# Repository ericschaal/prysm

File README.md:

<p align="center">
  <strong>LED strips that follow your screen.</strong><br>
  Prysm reads the picture, works out a colour for each LED around the screen
  and sends those colours to WLED.
</p>

## What you need

- **A picture source:** an HDMI capture card, or a rooted LG webOS TV.
- **WLED** with LED strips around the screen.
- **For a capture card:** a Linux or macOS computer, such as a Raspberry Pi.

```text
HDMI → capture card → computer running Prysm → WLED → LEDs
LG TV running Prysm (full package) → WLED → LEDs
LG TV (slim package) → computer running Prysm → WLED → LEDs
```

## Install

| Where Prysm runs | Package | Guide |
| --- | --- | --- |
| Raspberry Pi OS, Debian, Ubuntu | `prysm-headless` `.deb` (arm64, amd64) | [Debian](docs/users/debian.md) |
| Any Linux with Docker | `ghcr.io/ericschaal/prysm-headless` | [Docker](docs/users/docker.md) |
| TrueNAS SCALE | the same image | [TrueNAS](docs/users/truenas.md) |
| A rooted LG TV | `io.prysm.tv`, full or slim | [LG TV](docs/users/webos.md) |
| macOS, or Linux from source | build `prysm-headless` | [Build](docs/developers/README.md#build-and-run) |

Packages are attached to the [GitHub releases](https://github.com/ericschaal/prysm/releases).
Then connect the picture ([capture card](docs/users/quickstart.md) or
[LG TV](docs/users/webos.md)) and run the setup wizard in the web portal
([set up your lights](docs/users/configuration.md)). Start at
[Set up Prysm](docs/users/README.md) if you are unsure which setup fits.

The web portal has no password: keep Prysm on a trusted home network.

> **Status.** Prysm 1.x has not yet been verified end to end on real hardware
> (capture cards, WLED devices and both TV packages).

## What runs where

| Program | Runs on | Does |
| --- | --- | --- |
| `prysm-headless` | Linux or macOS | The service: capture card or slim TV in, WLED out, web portal. Shipped as the `.deb` and the Docker image. |
| `prysm-tui` | Linux or macOS | The same, plus a terminal preview of what the LEDs show; for local testing. |
| Full TV package | the TV | Captures, works out the colours, drives WLED and serves the web portal. |
| Slim TV package | the TV | Captures and sends the picture to `prysm-headless` on a computer. |

## In action

In the web portal you turn the lights on or off, switch between Screen sync
and WLED's own effects, watch a [live preview](docs/users/preview.md) of the
picture and the LED colours, and change settings.

## Develop Prysm

[Build and check](docs/developers/README.md) · [Architecture](docs/developers/architecture.md) ·
[Debugging](docs/developers/debugging.md) · [Contributing](docs/developers/guidelines.md)

[All documentation](docs/README.md) · [Research](research/README.md) ·
[Apache 2.0 license](LICENSE)

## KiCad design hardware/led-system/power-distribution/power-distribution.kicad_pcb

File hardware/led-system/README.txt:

Prysm LED system — revision C hobby prototype, 2026-10-09

Raspberry Pi 5 on its own USB-C supply; BTF SK9822 5V, 60 LEDs/m,
12mm black PCB, IP30, about 2.8m / 168 LEDs installed. The selected strip
variant is 45759013650658 (5m reel); do not power the full reel as this load.
LED supply: Mean Well LPV-100-5, 5V 12A / 60W — not 15A and not 100W.
User-selected limit: 75% LINEAR final LED output, applied in software.
This package documents that cap; it does not implement or enforce it.
No mains wiring is on these PCBs. This is a personal, supervised prototype.

REVISION C CHANGES AND STATUS
Three PCBs: GPIO interface 65x30mm; DC distribution 75x80mm; bottom-right
corner interface 65x40mm. ISO7720FD isolated level translators replace the
AHCT125 and the passive bottom-right L. Both supplies and both grounds at
that corner remain separate on the corner board. The strip groups' grounds
meet only at the distribution board through their heavy return cables.
The GPIO board separates Pi ground from the LED ground, including grounds
reached through Pi USB/HDMI. The separate distribution-to-GPIO logic cable
and F4/J4 were removed. Each translator side gets power and ground from
its local source/receiver, avoiding an independently fused logic supply that
could fail while leaving driven inputs on an unpowered IC.

The two BTF T injection corners are retained as requested. Their internal
mapping, contact current capability and pad fit are NOT verified. BTF's
inspected listing supplies no current rating. These are commissioning
blockers, not a declaration that the connectors are unsuitable or safe.
The CAD/package checks cover actual nets, footprints, routing and exports;
physical temperature, voltage, fault response, pad fit and cooler clearance
still require the tests below. This revision has not been physically tested.

SIGNAL AND POWER TOPOLOGY (viewed from behind the TV)
One directed chain, following the actual strip arrows:
  Pi -> GPIO J3 -> TOP -> T at top-right -> RIGHT
     -> corner PCB J1 (A input) -> J2 (B output) -> BOTTOM
     -> T at bottom-left -> LEFT -> unused final DO/CO
Leave the top-left start/end gap OPEN. Insulate the LEFT output pads.
Never join LEFT DO/CO back to TOP DI/CI. Do not fit a parallel passive L at
bottom-right: it would bypass the isolator and join the power/ground groups.
The user-approved active corner replaces that L; no L connector is now used.
If all four geometric corners must later connect, move the signal gap to a
straight section and redesign power grouping/feeds before connecting it.

  Corner       Connection                           Power arm
  Top-right    TOP DO/CO -> RIGHT DI/CI, group A     +5V_A and GND only
  Bottom-left  BOTTOM DO/CO -> LEFT DI/CI, group B   +5V_B and GND only
  Bottom-right Active A-to-B corner PCB; no bypass   None
  Top-left     Open end/start gap                    None

Distribution J2 -> top-right T: A = TOP + RIGHT.
Distribution J3 -> bottom-left T: B = BOTTOM + LEFT.
A and B positives must not join downstream of F2/F3. No A-to-B GND bridge
is permitted in the strip/corner harness either: it would give LED current
an alternative return through strip copper if a heavy return disconnected.
The corner isolator transfers signals without a conducting data/clock path
between groups. Opening a branch fuse removes that group's LED and local
translator power together. Missing local return cannot make a DC LED return
through Pi, the opposite strip, or data/clock pins across an isolator.
This is low-voltage return-path separation, NOT a mains isolation design.
Keep strip copper, mounting hardware and module grounds off TV metalwork.

T CONNECTORS AND REMOVABLE POWER ARMS
Select T shape / 4pin / 12mm explicitly. The older linked variant
45648064020706 selected L / 4pin / 12mm / 10sets when inspected; it is NOT
an ordering link for the intended T. X may be used only after the same
mapping checks; its fourth arm stays unused and insulated.
The strip is IP30 (no waterproof sleeve). Width alone does not establish
pad spacing, insertion depth, contact pressure, or polarity compatibility.
Ignore analog RGB markings. With the actual strip facing the intended way,
identify every connector arm/contact by continuity to actual strip labels:
  upstream DO -> downstream DI; upstream CO -> downstream CI;
  +5 -> +5; GND -> GND; no cross-connections and no joined outputs.
Record the complete mapping before power. There must be exactly one
upstream strip output and one downstream strip input per T. Never attach
an LED section to the power arm, even if its power wiring is correct.

A clip arm accepts a strip tongue, not loose wires. Use a sacrificial piece
of this exact 12mm strip PCB as a blank power tongue: remove all LEDs/ICs
and other components; cut/isolate the DATA/CLOCK tracks beyond their contact
pads; verify there is no connected active circuitry and no path from those
pads to either power lead. Solder short 16AWG +5/GND leads to the identified
power copper outside the clamp area. Keep solder and insulation out of the
contacts and preserve the original contact surface. If the remaining power
copper or pad is too small/fragile for a sound joint, this adapter has NOT
passed: obtain a purpose-made matching blank tongue before commissioning.
Do not invent a pad footprint from the advertised width.

Each power tongue has an XT30U-M pigtail; the energized branch cable has
XT30U-F recessed contacts. Two matched inline pairs total. The T's power
arm DATA/CLOCK pads have no attached conductors or LEDs; internal unloaded
stubs on the T do not create a second LED chain. Sleeve the soldered tongue
and capacitor leads, anchor the cable independently, and leave the clip
accessible. The XT30 disconnect lets the T/tongue remain fitted during
removal. Both supplies OFF before any connector is unplugged.
Fit one 1000uF 10V capacitor across each power tongue's +5/GND, insulated.
Do not treat the capacitor or brightness setting as connector protection.

LOAD, SUPPLY AND FUSES
168 x 0.06A = 10.08A nominal uncapped white, about 5.04A per equal group.
At 75% linear output the estimate is 7.56A total / 3.78A per equal group,
plus idle/logic current and real strip variation. This estimates average
load, not guaranteed peak/RMS current: LED PWM can retain full pulse
amplitude, and contact heating must be measured. Keep an upper design count
of 90 LEDs/group, 180 total (5.4A/group, 10.8A uncapped). Count actual cuts.
Size harnesses for uncapped operation; software is not fault protection.
Apply the cap at final pixel output, including startup and test effects.

LPV-100-5 delivers 12A through 40C ambient at rated input; its 5V-model curve
derates above 40C to 60% at 70C. At 50C the curve is about 10.4A available.
Allow ventilation and measure temperature behind the TV. Output tolerance
is +/-8% including line/load: 4.6..5.4V before wiring losses. Verify loaded
voltage at all strip ends; do not raise voltage to hide an excessive drop.
Its overload mode is automatic-retry hiccup at 110..150% of rated power.
Fuses may not clear under a current-limited/hiccup supply. F1 and the inline
15A fuse are NOT 12A overload limiters or selective protection. The 297
7.5A fuse may take up to 600s at 135% and up to 5s at 200%, under datasheet
conditions. Continuous fuse capability also falls with ambient temperature.
No claim is made that these fuses protect every PCB neck, strip IC, or
resistive connector fault. Poor contacts can overheat below fuse rating.

F1=15A; F2/F3=7.5A, Littelfuse 297 MINI blade, Keystone 3568 holders.
An additional inline 15A MINI fuse stays near PSU positive for input cable
protection, in a Littelfuse 0FHM0001SXJ covered MINI holder (20A/58VDC,
14AWG GXL leads). Its wires are black: mark both POSITIVE ends with red
sleeves before wiring. It has no guaranteed discrimination from F1. The old 2A logic
fuse and logic power cable are omitted; isolated logic supplies are local.
Insulated, anchored short wiring plus the LPV protection are part of this
prototype, with fault-current/temperature qualification still required.

CONNECTORS, WIRES AND LOCAL LOGIC POWER
Distribution J1: AMASS XT30UPB-M, pin1=GND, pin2=+5V_IN. Mate XT30U-F;
check molded polarity. PSU output is red+, black- (factory14AWG leads).
Use 14AWG copper total main pair target <=0.5m, including factory leads.
Distribution J2/J3: JST VH2 pin1=+5V_A/B, pin2=GND. VHR-2N mates,
SVH-41T-P1.1 contacts; 16AWG copper pair, target <=1m per branch.
JST specifies 10A with 16AWG under its test conditions; that is not a
rating for the BTF clips or the whole assembled harness.

GPIO J3 and corner J1/J2: JST VH4, same assigned contact order:
  1 = LOCAL strip +5V; 2 = DATA; 3 = CLOCK; 4 = LOCAL strip GND.
VHR-4N with SVH-41T-P1.1 contacts:16AWG power/ground,20AWG DATA/CLOCK.
Use copper wire with insulation rated >=105C and supplier current ratings
suited to the upstream fuse. No copper-clad aluminium or Dupont contacts.
Solder each four-wire pigtail to the identified strip pads, anchor it, and
insulate each conductor. Removability is at the VH connector, not by pulling
soldered strip pads. Keep GPIO-to-TOP <=30cm and each corner pigtail <=10cm;
route DATA/CLOCK close to its local GND. Solder tails must not touch TV metal.

GPIO J3 connects ONLY to the TOP INPUT end's local four pads. Its +5/GND
power only U1's output side. There is NO distribution-to-GPIO connection.
Corner J1 connects ONLY to RIGHT OUTPUT pads (local A rail and ground).
Corner J2 connects ONLY to BOTTOM INPUT pads (local B rail and ground).
These pigtails power only the small local isolator sections, never an LED
feed. Do not add cross-ground straps, shields bonded at both domains, or
any passive strip bridge around the corner module.

ISO7720FD (D8 narrow SOIC):1=VCC1,2=INA,3=INB,4=GND1,5=GND2,
6=OUTB,7=OUTA,8=VCC2. Use the default-LOW F variant and two forward channels;
ISO7721 or default-high ISO7720 are not substitutions. TI specifies
2.25..5.5V supply/level translation, default low with input-power loss,
and high impedance with output-power loss. Inputs require their own local
power; do not introduce separately switched/fused isolator-only rails.
Pi GPIO10/physical19=MOSI; GPIO11/physical23=SCLK; physical6=Pi GND;
physical1 supplies only U1's Pi side at3.3V. Pi5V pins2/4 remain NC.
10k input pulldowns and33ohm output resistors are fitted on both interfaces.
Each IC side has its own adjacent100nF bypass and local copper planes.
Start SPI mode0 at1MHz; framing and colour order must match this strip.
No chip select is required. Default-low behavior does not guarantee absence
of every power-ramp glitch; send an all-black frame before enabling effects.

ASSEMBLY AND FABRICATION
Open the three .kicad_pro files in KiCad10. Embedded symbols, local symbol
libraries and standard embedded footprints are included. Order2 layers,
FR4,1.6mm, mask both sides, lead-free HASL or ENIG. Distribution2oz BOTH
sides; GPIO/corner1oz both. Gerbers and separate PTH/NPTH Excellon files
are in each fabrication directory and its matching fabrication.zip.
Use prysm-led-system-rev-c.zip; revision B is superseded.

Only U1 on each interface is surface mount (SOIC8,1.27mm lead pitch).
Hand solder with flux and inspect all pins under magnification. Follow pin1
marking; DO NOT install the old PDIP14 AHCT125. Other parts are through-hole.
GPIO J1 is the ONLY underside component. Its pin1/square pad matches the
KiCad Pi uHAT convention; install Samtec ESQ-120-23-G-D below the PCB.
The socket body is16.13mm; actual mated spacing and4.83mm tail protrusion
must be checked with the Pi5 cooler/fan plug. GPIO holes are58mm apart.
Use M2.5 insulating spacers without forcing socket engagement or bending.
Corner and distribution boards use four insulated M2.5 mounting points.
Keep board undersides covered/clear of TV metal; retain airflow and access.
The generic socket3D model does not validate the selected tall socket fit.

Distribution C1 and both corner power capacitors: Panasonic EEU-FR1A102,
1000uF10V, D10xH16mm,5mm lead pitch. Square PCB pad is+. Negative stripe
faces GND. Fully solder all high-current connector/holder pins and inspect.
Crimp with the exact-terminal tool, perform pull tests, heat-shrink each
conductor, and provide anchors so no cable load reaches strip copper.

COMMISSIONING — RECORD ACTUAL VALUES BEFORE TV INSTALLATION
1. Supplies disconnected: inspect soldering, polarity, U1 pin1 and caps.
   Prove each T's four-contact mapping in its installed orientation, the
   power tongue's two-wire-only connection, and the open top-left signal gap.
   For A/B POSITIVE isolation remove F2 AND F3: upstream bus otherwise joins
   their fuse inputs. To verify no harness GND bridge, also unplug both VH2
   branches from distribution. The standalone corner must not have a DC
   A-to-B power/ground connection. Verify Pi GND-to-LED GND isolation too.
2. Use a current-limited bench5V supply initially, if available. Verify each
   branch and translator domain before attaching Pi. Establish Pi3.3V side
   and both local strip supplies; confirm no header5V back-power path.
3. Test a few LEDs dim red/green/blue, then all168. Verify colour order and
   one linear chain, with no reflected/parallel strip branch. Apply75% cap.
4. Measure main and branch currents at capped all-white and actual effects.
   Measure supply, both injections and all remote strip end voltages. Scope
   DATA/CLOCK at first TOP and first BOTTOM inputs for clean thresholds and
   overshoot relative to LOCAL supply/ground. Confirm supply never exceeds
   5.5V at isolators; obtain the actual SK9822 input/output limits if available.
5. Run to thermal equilibrium at the intended maximum ambient with the75%
   cap. Log T input and each strip-arm contact, power tongue, XT30, VH, fuse
   holders, wires, copper and supply temperatures. Check voltage across each
   connector to find contact resistance. No rating exists for BTF in the
   inspected listing: obtain manufacturer data or conservatively qualify the
   exact assembled sample, including repeated insertions and strain relief.
   An average3.78A estimate alone does not establish a safe T current limit.
6. On a current-limited bench, test Pi-only, LEDs-only, F2-open, F3-open and
   each branch-return-open case. Check isolated sides do not get parasitic
   power and no opposite branch/Pi wire becomes an LED return. Power OFF
   before reconfiguring each test; no live unplugging or intentional shorts
   against the full LPV supply. Fault-current/fuse-clearing tests need a
   controlled load, appropriate instrumentation and a nonflammable bench.
7. Dry-fit the real cooler/socket, pigtails and clips; test removal/reassembly
   without stressing strip pads. Mount behind TV only after those checks.

VALIDATION AND REBUILD
Use KiCad10.0.7's bundled Python (pcbnew), e.g. on this Mac:
  /Applications/KiCad/KiCad.app/Contents/Frameworks/Python.framework/Versions/Current/bin/python3 build.py
build.py is the CAD source of truth and OVERWRITES its generated CAD, reports,
previews, fabrication files and ZIPs. Edit the generator before rebuilding;
manual CAD edits must be transferred back to it. Routing tie-breaks and board
UUIDs are deterministic. All three boards are regenerated, then fresh ERC,
DRC with zone refill/parity and actual schematic/PCB pin-map checks run.
The script exports and packages only after checks pass. KiCad default ignored
rule classes still exist; no project-specific exclusions were added.

Run the same bundled Python with verify.py for fresh checks in temporary
storage, actual CAD net/footprint inspection, and SHA256/ZIP consistency.
It does not trust saved reports alone. build-manifest.json binds exported
files and reports to their generator/CAD/docs; changing them requires rebuild.
Exact CAD regeneration has been compared independently. KiCad reports do not
prove thermal performance, fault protection or the external harness mapping.

MANUFACTURER REFERENCES (reviewed2026-10-09)
Strip and selected variant:
https://www.btf-lighting.com/en-intl/products/1-sk9822-led-pixel-strip-data-and-clock-dc5v?variant=45759013650658
T/L/X connector family (select T4pin12mm manually; no published current rating):
https://www.btf-lighting.com/en-intl/products/2pin-3pin-4pin-5pin-corner-connector-8mm-10mm-12mm-width-t-l-x-shape-solderless-connector-ws2811-ws2812b-led-strip-no-soldering
Mean Well LPV-100:5V model table, overload, voltage tolerance,5V derating curve:
https://www.meanwell.com/Upload/PDF/LPV-100/LPV-100-SPEC.PDF
ISO7720/ISO7720F: D8 pinout§5, supply limits§6.3, power-loss modes§8.4,
decoupling§10. No mains safety claim is made for these boards:
https://www.ti.com/lit/ds/symlink/iso7720.pdf
JST VH: B2P/B4P-VH, VHR-2N/4N, SVH-41T-P1.1 (20–16AWG),10A at16AWG:
https://www.jst-mfg.com/product/pdf/eng/eVH.pdf
AMASS XT30UPB-M (manufacturer20A test rating with16AWG; mating must match):
https://www.china-amass.net/xt30upb-m-product/
Keystone3568 MINI fuse holder:
https://www.keyelco.com/product.cfm/product_id/306
Littelfuse 0FHM0001SXJ inline holder (20A/58VDC, 14AWG):
https://www.littelfuse.com/assetdocs/littelfuse-fuse-holder-mini-fhm-datasheet.pdf?assetguid=339fa35e-eabc-45c5-9093-8abceaa8a2cf
Littelfuse297 MINI ratings and time/current/temperature curves:
https://www.littelfuse.com/assetdocs/littelfuse-datasheet-297-mini32v?assetguid=42c9dd21-a88e-4328-8e67-2f832444faf1
Samtec ESQ-120-23-G-D:
https://www.samtec.com/products/esq-120-23-g-d
Panasonic EEU-FR1A102:
https://industrial.panasonic.com/ww/products/pt/aluminum-cap-lead/models/EEUFR1A102
Pi SPI0:
https://www.raspberrypi.com/documentation/computers/raspberry-pi.html#spi0
Pi5 cooler drawing:
https://datasheets.raspberrypi.com/cooling/raspberry-pi-active-cooler-mechanical-drawing.pdf

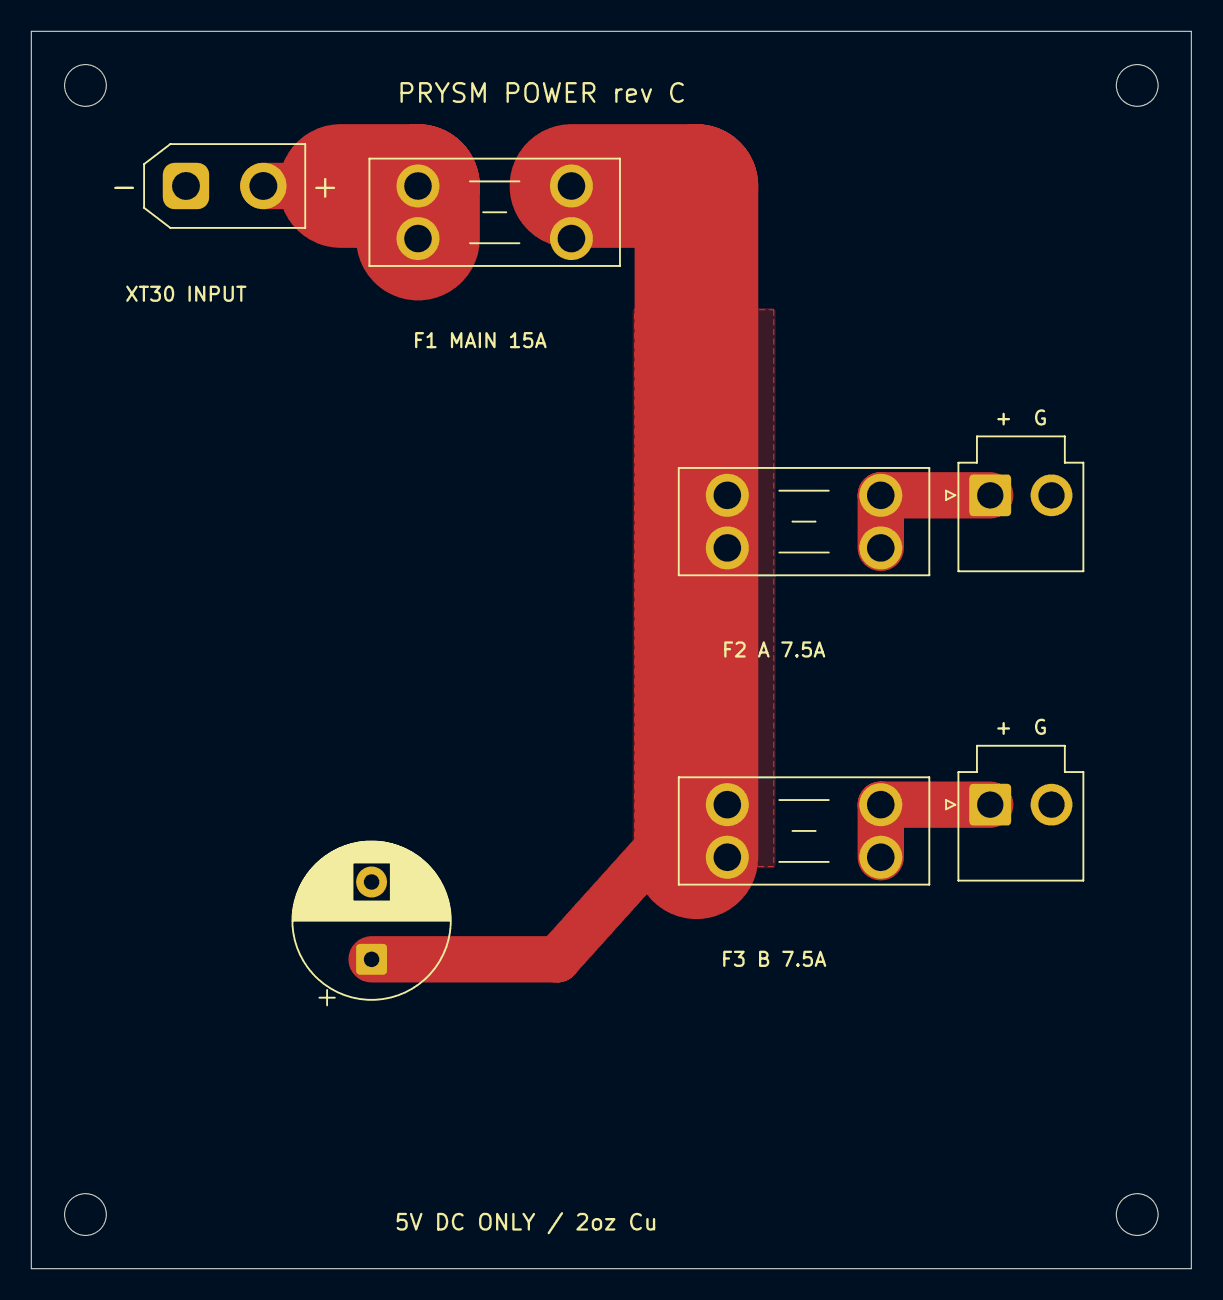
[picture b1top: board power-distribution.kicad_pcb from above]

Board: 2 copper layers, 75.0 x 80.0 mm, 11 parts (0 on the bottom side), 5 nets.

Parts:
C1: 1000uF 10V; CP_Radial_D10.0mm_P5.00mm
F1: 15A MINI; Fuseholder_Blade_Mini_Keystone_3568
F2: 7.5A MINI / GROUP A; Fuseholder_Blade_Mini_Keystone_3568
F3: 7.5A MINI / GROUP B; Fuseholder_Blade_Mini_Keystone_3568
H1, H2, H3, H4: MountingHole_2.7mm_M2.5
J1: 5V INPUT / XT30; AMASS_XT30UPB-M_1x02_P5.0mm_Vertical
J2: GROUP A / VH2; JST_VH_B2P-VH-B_1x02_P3.96mm_Vertical
J3: GROUP B / VH2; JST_VH_B2P-VH-B_1x02_P3.96mm_Vertical

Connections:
+5V_A: F2.2, J2.1
+5V_B: F3.2, J3.1
+5V_BUS: C1.1, F1.2, F2.1, F3.1
+5V_IN: F1.1, J1.2
GND: C1.2, J1.1, J2.2, J3.2

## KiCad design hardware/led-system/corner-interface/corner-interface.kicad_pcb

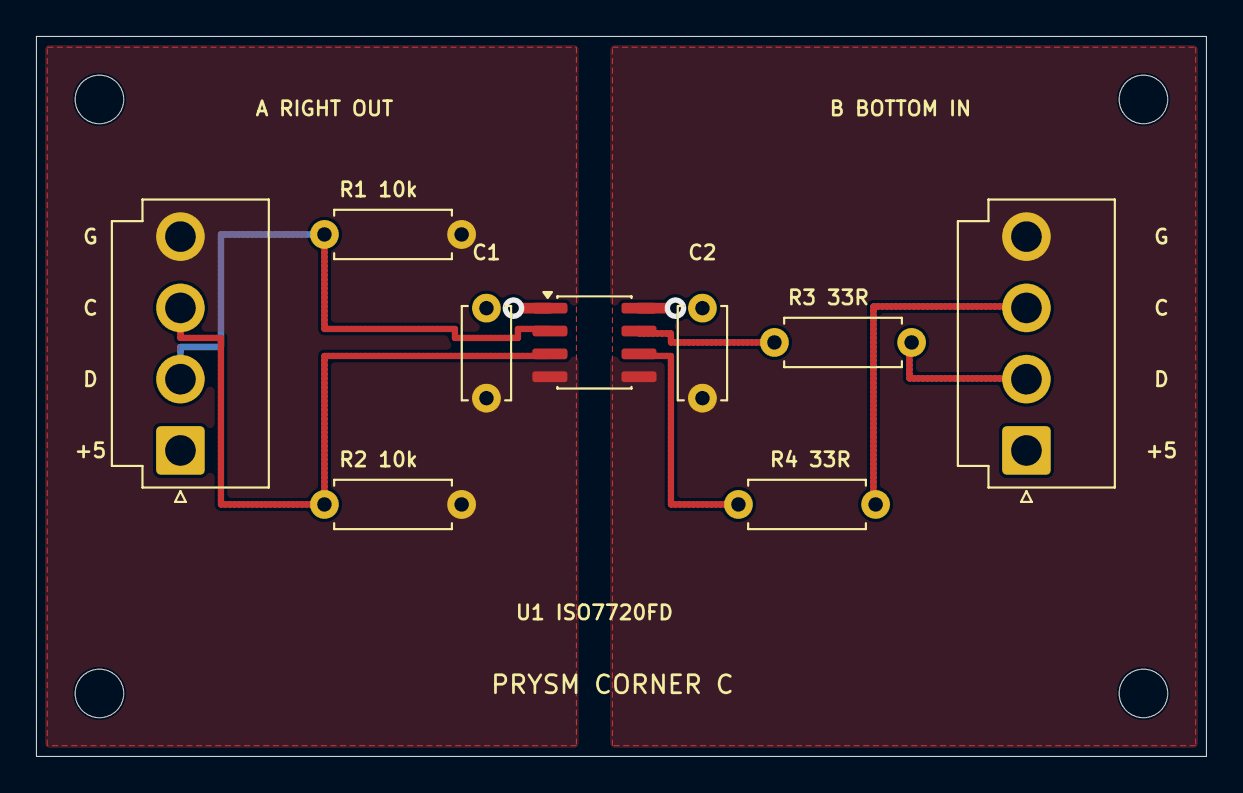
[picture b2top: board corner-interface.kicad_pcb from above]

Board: 2 copper layers, 65.0 x 40.0 mm, 13 parts (0 on the bottom side), 10 nets.

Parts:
C1, C2: 100nF 16V; C_Disc_D5.0mm_W2.5mm_P5.00mm
H1, H2, H3, H4: MountingHole_2.7mm_M2.5
J1: RIGHT OUT + D C G; JST_VH_B4P-VH_1x04_P3.96mm_Vertical
J2: BOTTOM IN + D C G; JST_VH_B4P-VH_1x04_P3.96mm_Vertical
R1, R2: 10k; R_Axial_DIN0207_L6.3mm_D2.5mm_P7.62mm_Horizontal
R3, R4: 33R; R_Axial_DIN0207_L6.3mm_D2.5mm_P7.62mm_Horizontal
U1: ISO7720FD; SOIC-8_3.9x4.9mm_P1.27mm

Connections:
+5V_A: C1.1, J1.1, U1.1
+5V_B: C2.1, J2.1, U1.8
CLOCK_A: J1.3, R2.1, U1.3
CLOCK_B: J2.3, R4.2
CLOCK_RAW: R4.1, U1.6
DATA_A: J1.2, R1.1, U1.2
DATA_B: J2.2, R3.2
DATA_RAW: R3.1, U1.7
GND_A: C1.2, J1.4, R1.2, R2.2, U1.4
GND_B: C2.2, J2.4, U1.5

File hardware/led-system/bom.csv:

Assembly,References,Quantity,Manufacturer,Part number,Specification,Notes
GPIO PCB,J1,1,Samtec,ESQ-120-23-G-D,2x20 female socket 2.54mm pitch 16.13mm body,Underside only; verify actual Pi cooler and tail clearance
GPIO PCB,U1,1,Texas Instruments,ISO7720FDR,Default-LOW dual forward isolator SOIC8 D package,FD device; R is reel packaging; not ISO7721 or non-F version
GPIO PCB,R1 R2,2,Generic,10k 1% 0.25W axial,Body <=6.3x2.5mm;7.62mm lead pitch,Pi-side input pulldowns
GPIO PCB,R3 R4,2,Generic,33ohm 1% 0.25W axial,Body <=6.3x2.5mm;7.62mm lead pitch,Output source series resistors
GPIO PCB,C1 C2,2,Generic,100nF ceramic radial >=16V,5mm pitch;body <=5mm diameter x2.5mm thick,Prefer X7R; one per isolated IC side
GPIO PCB,J3,1,JST,B4P-VH,4-pin VH 3.96mm vertical header,1 local TOP+5;2 DATA;3 CLOCK;4 local TOP GND
Corner PCB,U1,1,Texas Instruments,ISO7720FDR,Default-LOW dual forward isolator SOIC8 D package,Input side A;output side B; no A/B ground or power bridge
Corner PCB,R1 R2,2,Generic,10k 1% 0.25W axial,Body <=6.3x2.5mm;7.62mm lead pitch,Group-A input pulldowns
Corner PCB,R3 R4,2,Generic,33ohm 1% 0.25W axial,Body <=6.3x2.5mm;7.62mm lead pitch,Group-B output source series resistors
Corner PCB,C1 C2,2,Generic,100nF ceramic radial >=16V,5mm pitch;body <=5mm diameter x2.5mm thick,Prefer X7R; one per local supply domain
Corner PCB,J1 J2,2,JST,B4P-VH,4-pin VH 3.96mm vertical header,1 local+5;2 DATA;3 CLOCK;4 local GND;J1 RIGHT output;J2 BOTTOM input
Distribution PCB,J1,1,AMASS,XT30UPB-M,Vertical through-hole XT30 5mm pitch,Pin1 GND;pin2 positive; verify molded polarity
Distribution PCB,J2 J3,2,JST,B2P-VH,2-pin VH 3.96mm vertical header,10A manufacturer condition at16AWG;pin1+5;pin2GND
Distribution PCB,F1 F2 F3,3,Keystone,3568,Through-hole MINI blade fuse holder,Not ATO or Micro2
Distribution PCB,F1,1,Littelfuse,0297015,297 MINI 15A 32V,Distributor packaging suffix to select; not a12A current limiter
Distribution PCB,F2 F3,2,Littelfuse,029707.5,297 MINI 7.5A 32V,Hiccup supply does not guarantee fuse clearing
Distribution PCB,C1,1,Panasonic,EEU-FR1A102,1000uF10V D10xH16mm pitch5mm,Polarized; negative to GND
Power harness,PSU main lead,1,AMASS,XT30U-F,Recessed energized-contact wire connector,14AWG copper cable;verify molded polarity
Power harness,Branch board mates,2,JST,VHR-2N,2-pin VH housing,One per fused injection branch
Power harness,Branch contacts,4,JST,SVH-41T-P1.1,20-16AWG VH crimp contact,Use16AWG copper power and ground
Power harness,T power-arm connections,2,AMASS,XT30U-F + XT30U-M matched pair,Removable inline power connection,F on energized branch;M on blank power tongue
Power harness,PSU cable fuse holder,1,Littelfuse,0FHM0001SXJ,Covered MINI holder20A58VDC;14AWG GXL black leads,Install in POSITIVE lead near PSU;mark black wires red;add15A297 fuse
Power harness,PSU cable fuse,1,Littelfuse,0297015,297 MINI15A32V,Additional to PCB F1; no selective-clearing claim
Power harness,Injection capacitors,2,Panasonic,EEU-FR1A102,1000uF10V D10xH16mm pitch5mm,Across each T power tongue+5/GND;insulate and anchor
Signal harness,GPIO J3 and corner J1 J2 mates,3,JST,VHR-4N,4-pin VH housing,1 local+5;2 DATA;3 CLOCK;4 local GND
Signal harness,Four-pin harness contacts,12,JST,SVH-41T-P1.1,20-16AWG VH crimp contact,16AWG power/GND;20AWG DATA/CLOCK
Cable,PSU to distribution,As measured,Generic,14AWG stranded copper red/black,>=105C insulation;target<=0.5m including PSU leads,Verify wire ampacity and insulation diameter;not CCA
Cable,Two injection feeds and local logic power leads,As measured,Generic,16AWG stranded copper red/black,>=105C insulation;target<=1m injection pair,Local logic leads come ONLY from adjacent strip pads
Cable,DATA CLOCK,As measured,Generic,20AWG stranded copper,>=105C insulation;fits SVH-41T-P1.1 contacts,GPIO<=30cm;each corner lead<=10cm;route with local GND
Mechanical,GPIO standoffs,2,Generic,M2.5 insulating spacers with screws,Height matched to actual socket engagement,Verify cooler and fan cable access
Mechanical,Distribution and corner standoffs,8,Generic,M2.5 insulating spacers with screws,Four per board,Insulate underside;retain airflow and fuse access
Assembly,Insulation and anchors,As needed,Generic,Adhesive-lined heat-shrink plus cable-tie anchors,Individual conductor insulation and external strain relief,No strip copper or component tails touching TV metal
External,LED supply,1,Mean Well,LPV-100-5,5V12A60W;derates above40C for5V model,Already selected;no mains design in this package
External,LED strip,1 reel,BTF-LIGHTING,Variant45759013650658,SK9822 5m60LED/m IP30 black PCB12mm,Install~2.8m168LED;max90per group;75%linear output cap
Corner harness,Top-right and bottom-left,2,BTF-LIGHTING,T shape /4pin12mm,Exact T order variant must be selected manually,Mapping and current rating UNVERIFIED;old45648064020706 is L
Corner harness,Two power-arm tongues,2,Matching strip PCB or verified custom blank,Passive12mm power tongue matching actual strip pads,ONLY+5 and GND leads;no active LED or DATA/CLOCK wiring,Provisional fabrication from sacrificial strip offcut;fit/current tests required

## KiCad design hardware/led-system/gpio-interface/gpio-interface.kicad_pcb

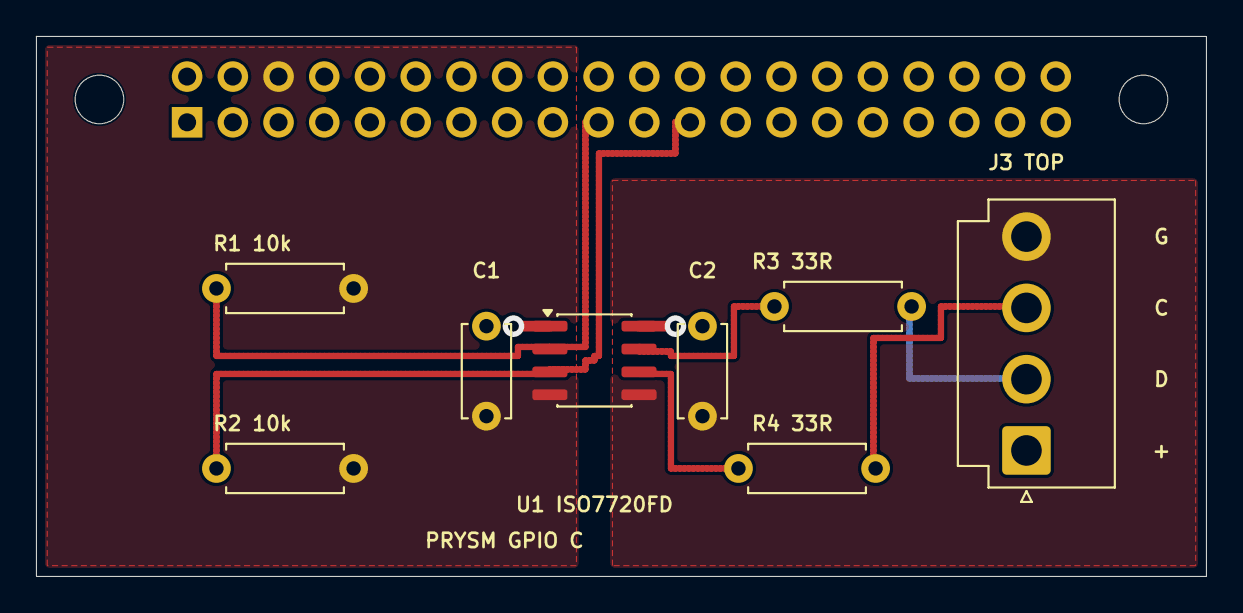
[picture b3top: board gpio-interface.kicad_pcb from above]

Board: 2 copper layers, 65.0 x 30.0 mm, 11 parts (1 on the bottom side), 10 nets.

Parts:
C1, C2: 100nF 16V; C_Disc_D5.0mm_W2.5mm_P5.00mm
H1, H2: MountingHole_2.7mm_M2.5
J1: Pi GPIO underside; PinSocket_2x20_P2.54mm_Vertical
J3: TOP LOCAL + D C G; JST_VH_B4P-VH_1x04_P3.96mm_Vertical
R1, R2: 10k; R_Axial_DIN0207_L6.3mm_D2.5mm_P7.62mm_Horizontal
R3, R4: 33R; R_Axial_DIN0207_L6.3mm_D2.5mm_P7.62mm_Horizontal
U1: ISO7720FD; SOIC-8_3.9x4.9mm_P1.27mm

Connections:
+3V3_PI: C1.1, J1.1, U1.1
+5V_A: C2.1, J3.1, U1.8
CLOCK_5V: J3.3, R4.2
CLOCK_RAW: R4.1, U1.6
DATA_5V: J3.2, R3.2
DATA_RAW: R3.1, U1.7
GND_A: C2.2, J3.4, U1.5
GND_PI: C1.2, J1.6, R1.2, R2.2, U1.4
MOSI_3V3: J1.19, R1.1, U1.2
SCLK_3V3: J1.23, R2.1, U1.3

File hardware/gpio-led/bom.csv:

Reference,Quantity,Value,Package,Note
U1,1,SN74AHCT125N,PDIP-14 7.62mm,TI pinout; accepts the bare DIP chip discussed
C1,1,100nF ceramic 16V or higher,Through-hole pitch TBD,Decoupling next to U1 pin 14
R1 R2,2,10k ohm 0.25W,Axial through-hole,Input pull-downs
R3 R4,2,33 ohm 0.25W,Axial through-hole,Source-series resistors beside outputs
J1,1,2x20 female GPIO socket 2.54mm,Through-hole underside,Tall socket height must match spacers and cooler clearance
J2,1,2-pin keyed logic-power connector,Through-hole footprint TBD,+5V_LED and GND; low-current branch only
J3,1,3-pin keyed signal connector,Through-hole footprint TBD,DATA CLOCK GND; no strip power
Hardware,2,Insulating spacer and screw,Size TBD,Match official Pi holes and socket height
